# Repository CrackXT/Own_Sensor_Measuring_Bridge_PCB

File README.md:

# Own_Sensor_Measuring_Bridge_PCB

PCB files for Sensor Measuring Bridge 

# Description

Allows the current consumption of sensors to be measured.

The board can be produced here (AISLER) with the files (.brd and .sch) or by any other PCB manufacturer. -> https://aisler.net/

# Serie

- .dev

# Layout

Top<br>

Bottom<br>

Routing/Dimensions(inch)<br>

Schematic<br>
Schematic as .pdf at the top of the page.

# License

Open hardware, use it, mod it, whatever you want, feel free...

# Thanks!

Own design and layout.

# Version - Build

v1.0 - 06.11.2022

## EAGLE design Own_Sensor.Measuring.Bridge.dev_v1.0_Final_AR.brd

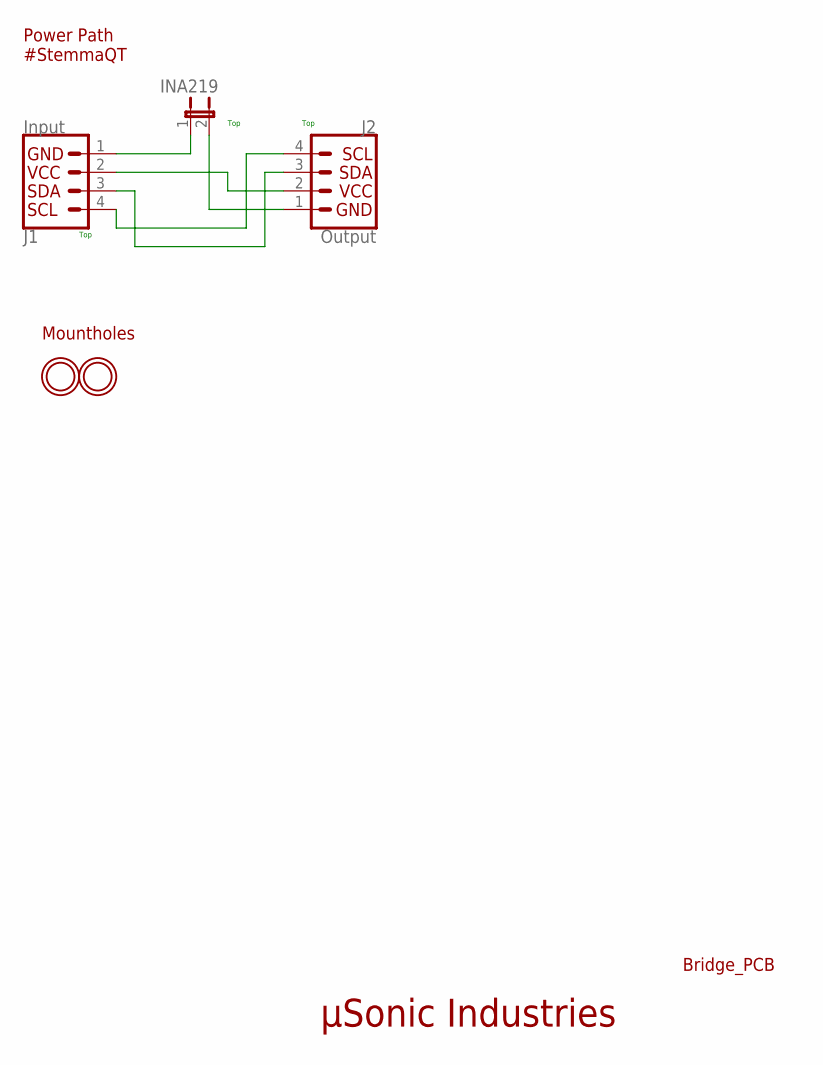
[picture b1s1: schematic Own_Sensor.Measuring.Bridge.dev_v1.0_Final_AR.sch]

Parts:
INA219: JP1E; JP1
J1: Input; JST04_1MM_RA
J2: Output; JST04_1MM_RA
U$18, U$19: MOUNTINGHOLE2.5; MOUNTINGHOLE_2.5_PLATED

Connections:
3V3: J1.2, J2.2
GND1: INA219.1, J1.1
GND2: INA219.2, J2.1
SCL: J1.4, J2.4
SDA: J1.3, J2.3

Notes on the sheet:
µSonic Industries
Bridge_PCB
Power Path #StemmaQT
Mountholes
Top

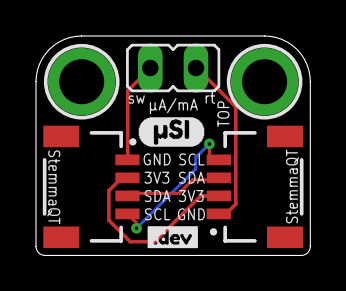
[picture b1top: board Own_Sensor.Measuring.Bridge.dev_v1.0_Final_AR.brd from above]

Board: 2 copper layers, 15.2 x 12.2 mm, 8 parts (1 on the bottom side), 5 nets.

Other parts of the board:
U$2: #DEV0
U$4: OSHW-LOGO-S
U$5: #SI0

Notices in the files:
parts and their libraries:
microbuilder: This work is placed in the public domain, and may be freely used for commercial and non-commercial work with the following conditions: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
SparkFun-Aesthetics: Licensing: Creative Commons ShareAlike 4.0 International - https://creativecommons.org/licenses/by-sa/4.0
